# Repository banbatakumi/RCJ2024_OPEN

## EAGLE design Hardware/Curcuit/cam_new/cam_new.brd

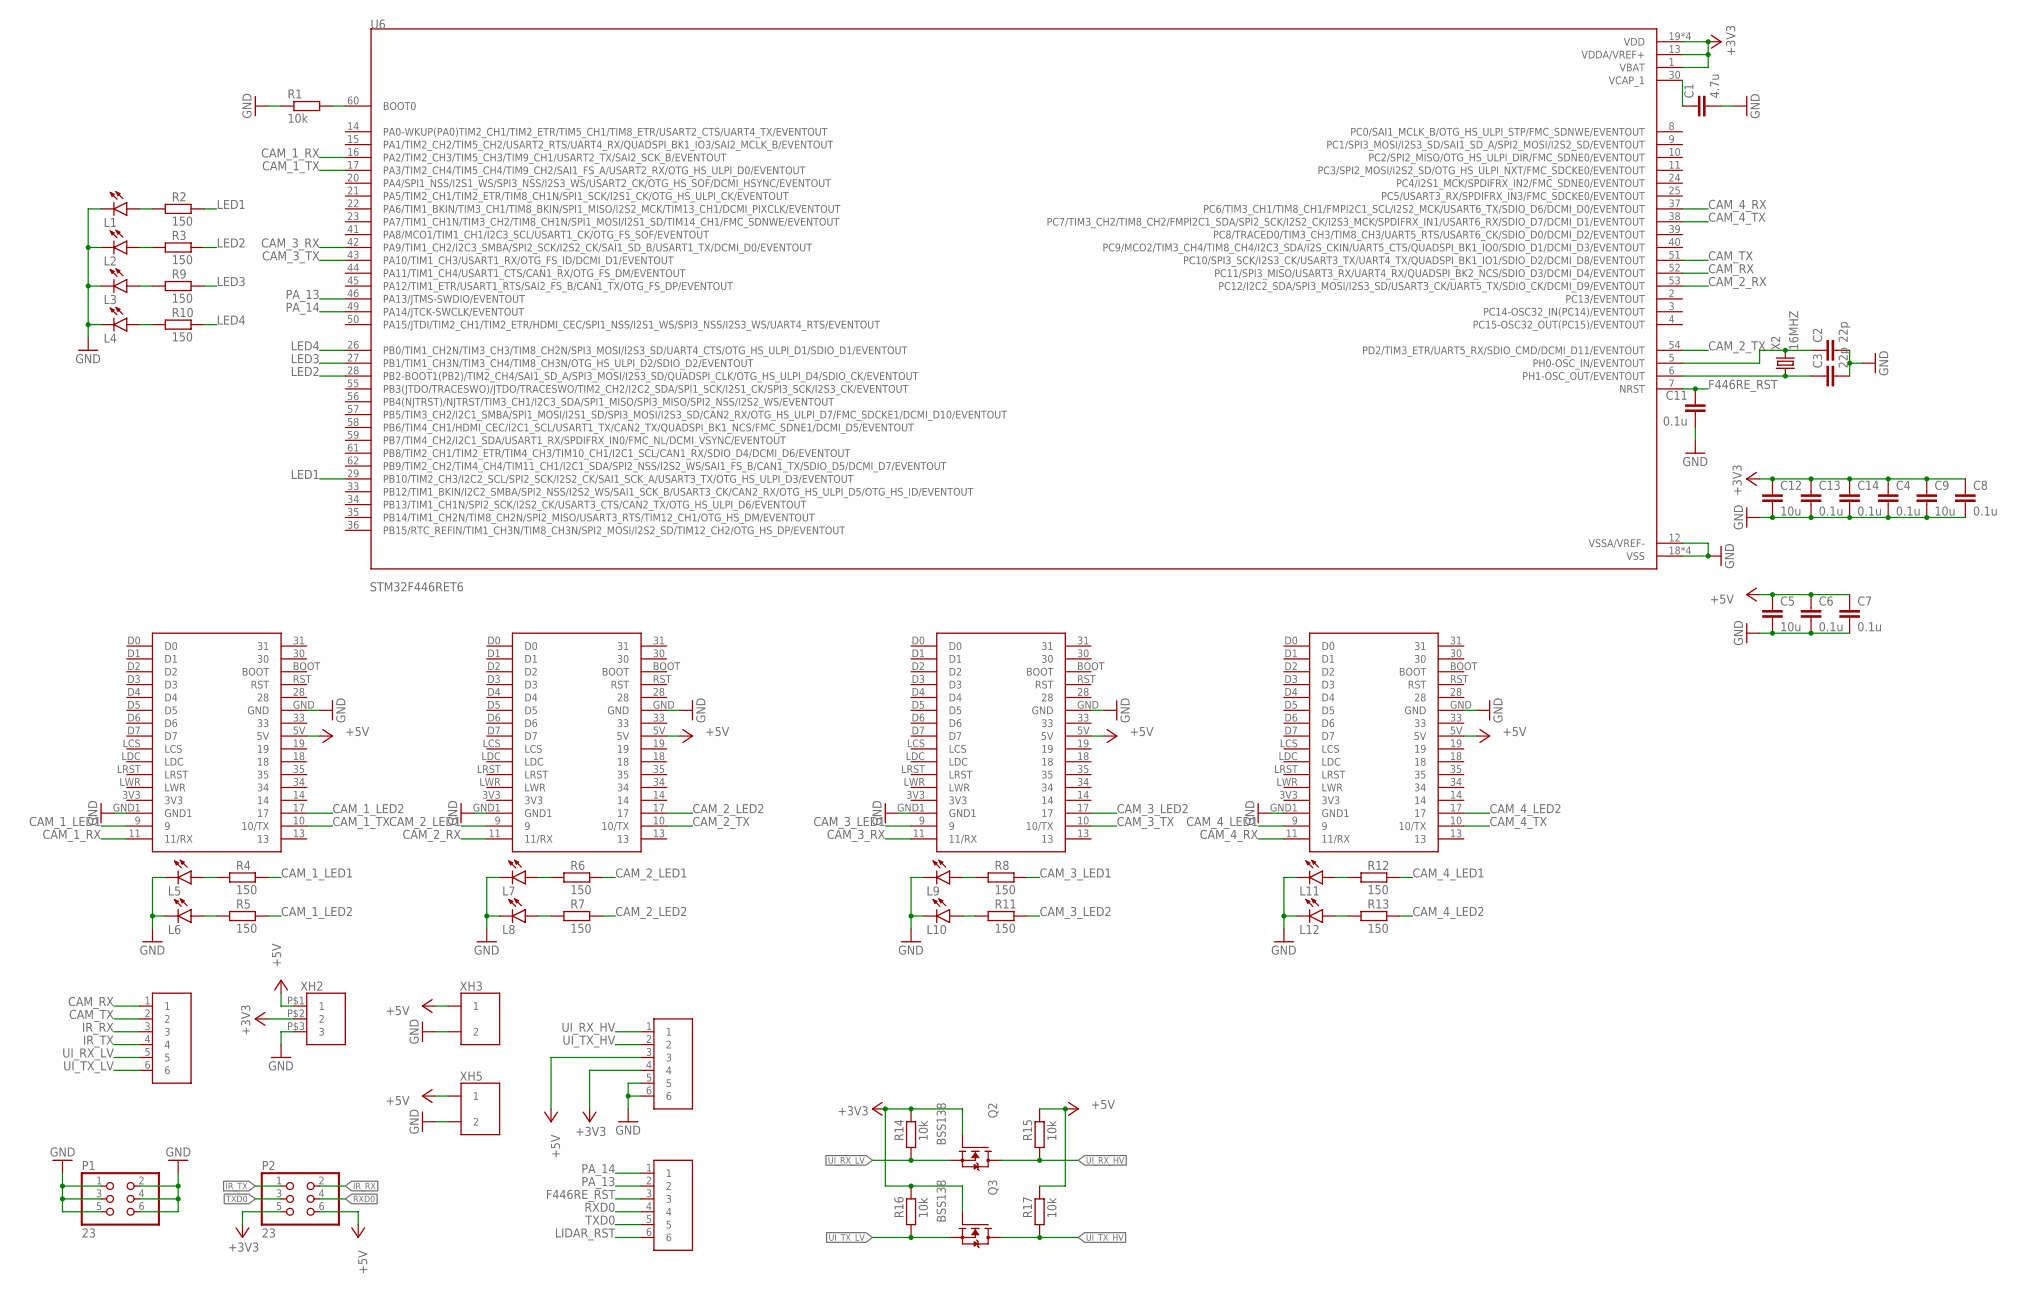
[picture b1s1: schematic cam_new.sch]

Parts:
C1: 4.7u; C0603
C2, C3: 22p; C0603
C4, C6, C7, C8, C11, C13, C14: 0.1u; C0603
C5, C9, C12: 10u; C0805
L1, L2, L3, L4, L5, L6, L7, L8, L9, L10, L11, L12: SML-E12P8WT86; LED_SML-LXFM0603SIC-TR
P1, P2: 23; 2*3
Q2, Q3: BSS138; SOT95P240X111-3N
R1, R14, R15, R16, R17: 10k; R0603
R2, R3, R4, R5, R6, R7, R8, R9, R10, R11, R12, R13: 150; R0603
U1, U2, U3, U4: M1N
U6: STM32F446RET6; QFP50P1200X1200X160-64N
X2: 16MHZ
XH1, XH4, XH6: 6B
XH2: 3B
XH3, XH5: 2B

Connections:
+3V3: C4.1, C8.1, C9.1, C12.1, C13.1, C14.1, P2.5, Q2.1 (G), Q3.1 (G), R14.2, R16.2, U6.1 (VBAT), U6.13 (VDDA/VREF+), U6.19 (VDD), U6.32 (VDD), U6.48 (VDD), U6.64 (VDD), XH2.P$2 (2), XH4.4
+5V: C5.1, C6.1, C7.1, P2.6, R15.2, R17.2, U1.5V, U2.5V, U3.5V, U4.5V, XH2.P$1 (1), XH3.P$1 (1), XH4.3, XH5.P$1 (1)
CAM_1_LED1: R4.2, U1.9
CAM_1_LED2: R5.2, U1.17
CAM_1_RX: U1.11 (11/RX), U6.16 (PA2/TIM2_CH3/TIM5_CH3/TIM9_CH1/USART2_T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)
CAM_1_TX: U1.10 (10/TX), U6.17 (PA3/TIM2_CH4/TIM5_CH4/TIM9_CH2/SAI1_FS_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)
CAM_2_LED1: R6.2, U2.9
CAM_2_LED2: R7.2, U2.17
CAM_2_RX: U2.11 (11/RX), U6.53 (PC12/I2C2_SDA/SPI3_MOSI/I2S3_SD/USART3_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)
CAM_2_TX: U2.10 (10/TX), U6.54 (PD2/TIM3_ETR/UART5_RX/SDIO_CMD/DCMI_D11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)
CAM_3_LED1: R8.2, U3.9
CAM_3_LED2: R11.2, U3.17
CAM_3_RX: U3.11 (11/RX), U6.42 (PA9/TIM1_CH2/I2C3_SMBA/SPI2_SCK/I2S2_CK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)
CAM_3_TX: U3.10 (10/TX), U6.43 (PA10/TIM1_CH3/USART1_RX/OTG_FS_ID/DCMI_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)
CAM_4_LED1: R12.2, U4.9
CAM_4_LED2: R13.2, U4.17
CAM_4_RX: U4.11 (11/RX), U6.37 (PC6/TIM3_CH1/TIM8_CH1/FMPI2C1_SCL/I2S2_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)
CAM_4_TX: U4.10 (10/TX), U6.38 (PC7/TIM3_CH2/TIM8_CH2/FMPI2C1_SDA/SPI2_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)
CAM_RX: U6.52 (PC11/SPI3_MISO/USART3_RX/UART4_RX/QUADS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), XH1.1
CAM_TX: U6.51 (PC10/SPI3_SCK/I2S3_CK/USART3_TX/UART4_T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), XH1.2
F446RE_RST: C11.1, U6.7 (NRST), XH6.3
GND: C1.2, C2.2, C3.2, C4.2, C5.2, C6.2, C7.2, C8.2, C9.2, C11.2, C12.2, C13.2, C14.2, L1.C, L2.C, L3.C, L4.C, L5.C, L6.C, L7.C, L8.C, L9.C, L10.C, L11.C, L12.C, P1.1, P1.2, P1.3, P1.4, P1.5, P1.6, R1.1, U1.GND, U1.GND1, U2.GND, U2.GND1, U3.GND, U3.GND1, U4.GND, U4.GND1, U6.12 (VSSA/VREF-), U6.18 (VSS), U6.31 (VSS), U6.47 (VSS), U6.63 (VSS), XH2.P$3 (3), XH3.P$2 (2), XH4.5, XH4.6, XH5.P$2 (2)
IR_RX: P2.2, XH1.3
IR_TX: P2.1, XH1.4
LED1: R2.2, U6.29 (PB10/TIM2_CH3/I2C2_SCL/SPI2_SCK/I2S2_CK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)
LED2: R3.2, U6.28 (PB2-BOOT1(PB2)/TIM2_CH4/SAI1_SD_A/SPI3_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)
LED3: R9.2, U6.27 (PB1/TIM1_CH3N/TIM3_CH4/TIM8_CH3N/OTG_HS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)
LED4: R10.2, U6.26 (PB0/TIM1_CH2N/TIM3_CH3/TIM8_CH2N/SPI3_M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)
LIDAR_RST: XH6.6
unnamed: C1.1, U6.30 (VCAP_1)
unnamed: R1.2, U6.60 (BOOT0)
unnamed: C2.1, U6.5 (PH0-OSC_IN/EVENTOUT), X2.P$2 (2)
unnamed: C3.1, U6.6 (PH1-OSC_OUT/EVENTOUT), X2.P$1 (1)
unnamed: L2.A, R3.1
unnamed: L4.A, R10.1
unnamed: L1.A, R2.1
unnamed: L6.A, R5.1
unnamed: L3.A, R9.1
unnamed: L5.A, R4.1
unnamed: L8.A, R7.1
unnamed: L7.A, R6.1
unnamed: L10.A, R11.1
unnamed: L9.A, R8.1
unnamed: L12.A, R13.1
unnamed: L11.A, R12.1
PA_13: U6.46 (PA13/JTMS-SWDIO/EVENTOUT), XH6.2
PA_14: U6.49 (PA14/JTCK-SWCLK/EVENTOUT), XH6.1
RXD0: P2.4, XH6.4
TXD0: P2.3, XH6.5
UI_RX_HV: Q2.3 (D), R15.1, XH4.1
UI_RX_LV: Q2.2 (S), R14.1, XH1.5
UI_TX_HV: Q3.3 (D), R17.1, XH4.2
UI_TX_LV: Q3.2 (S), R16.1, XH1.6

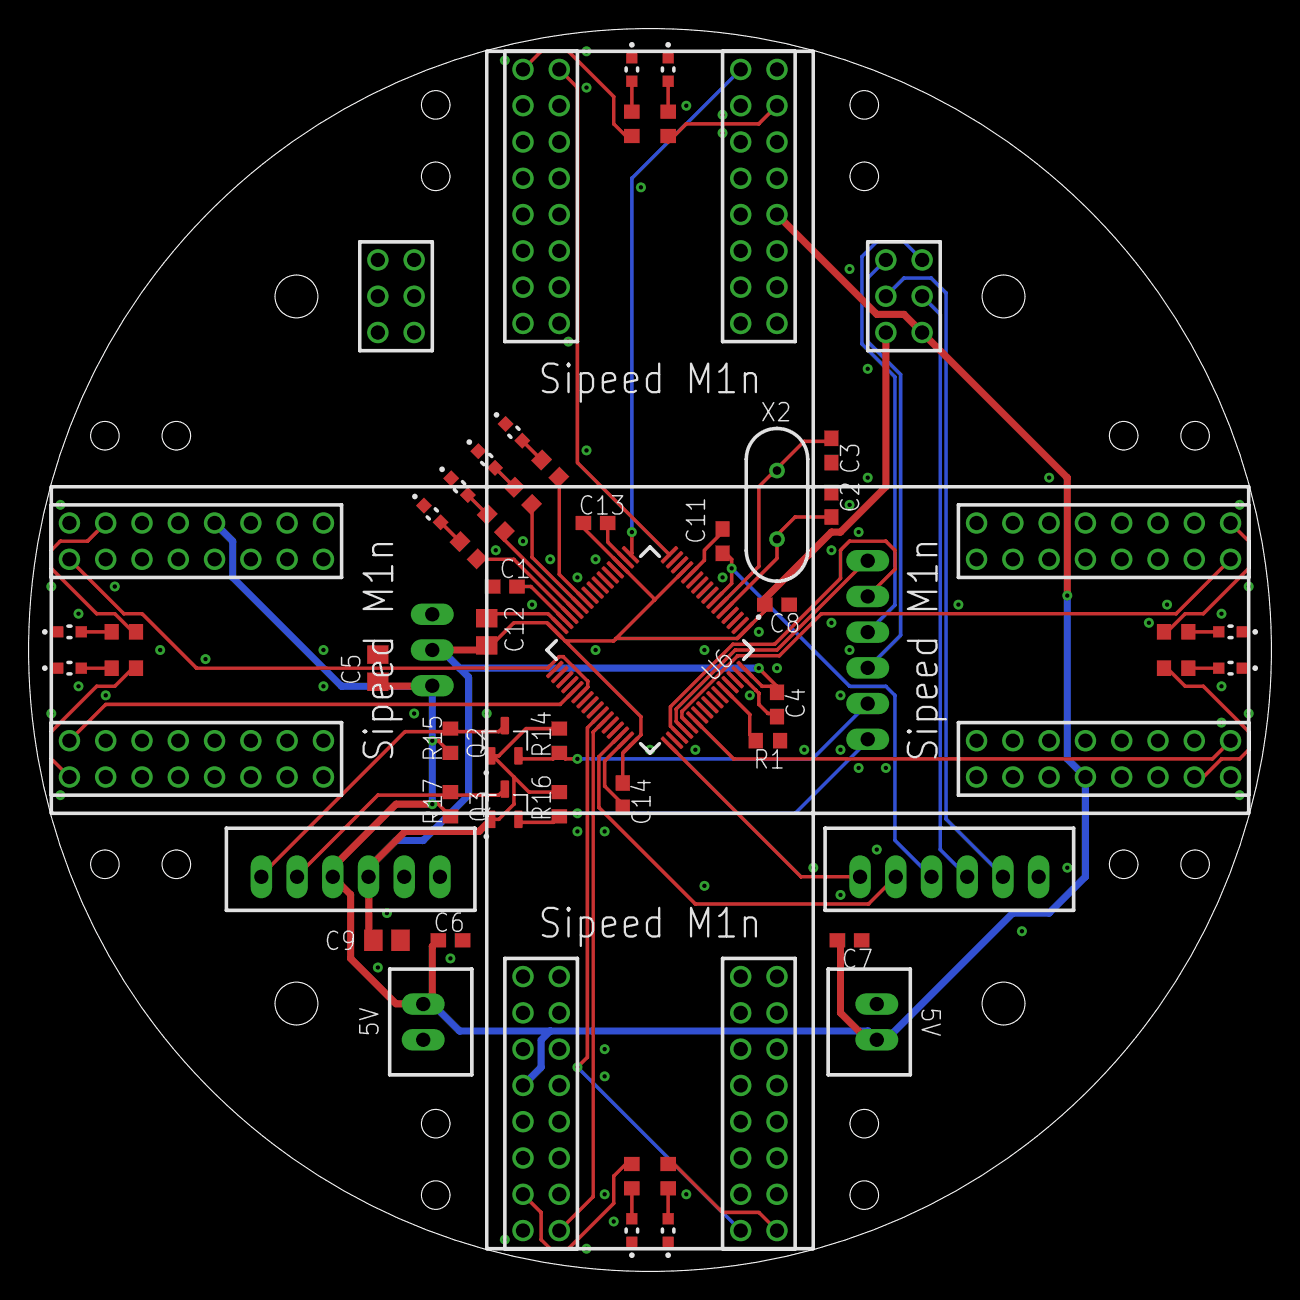
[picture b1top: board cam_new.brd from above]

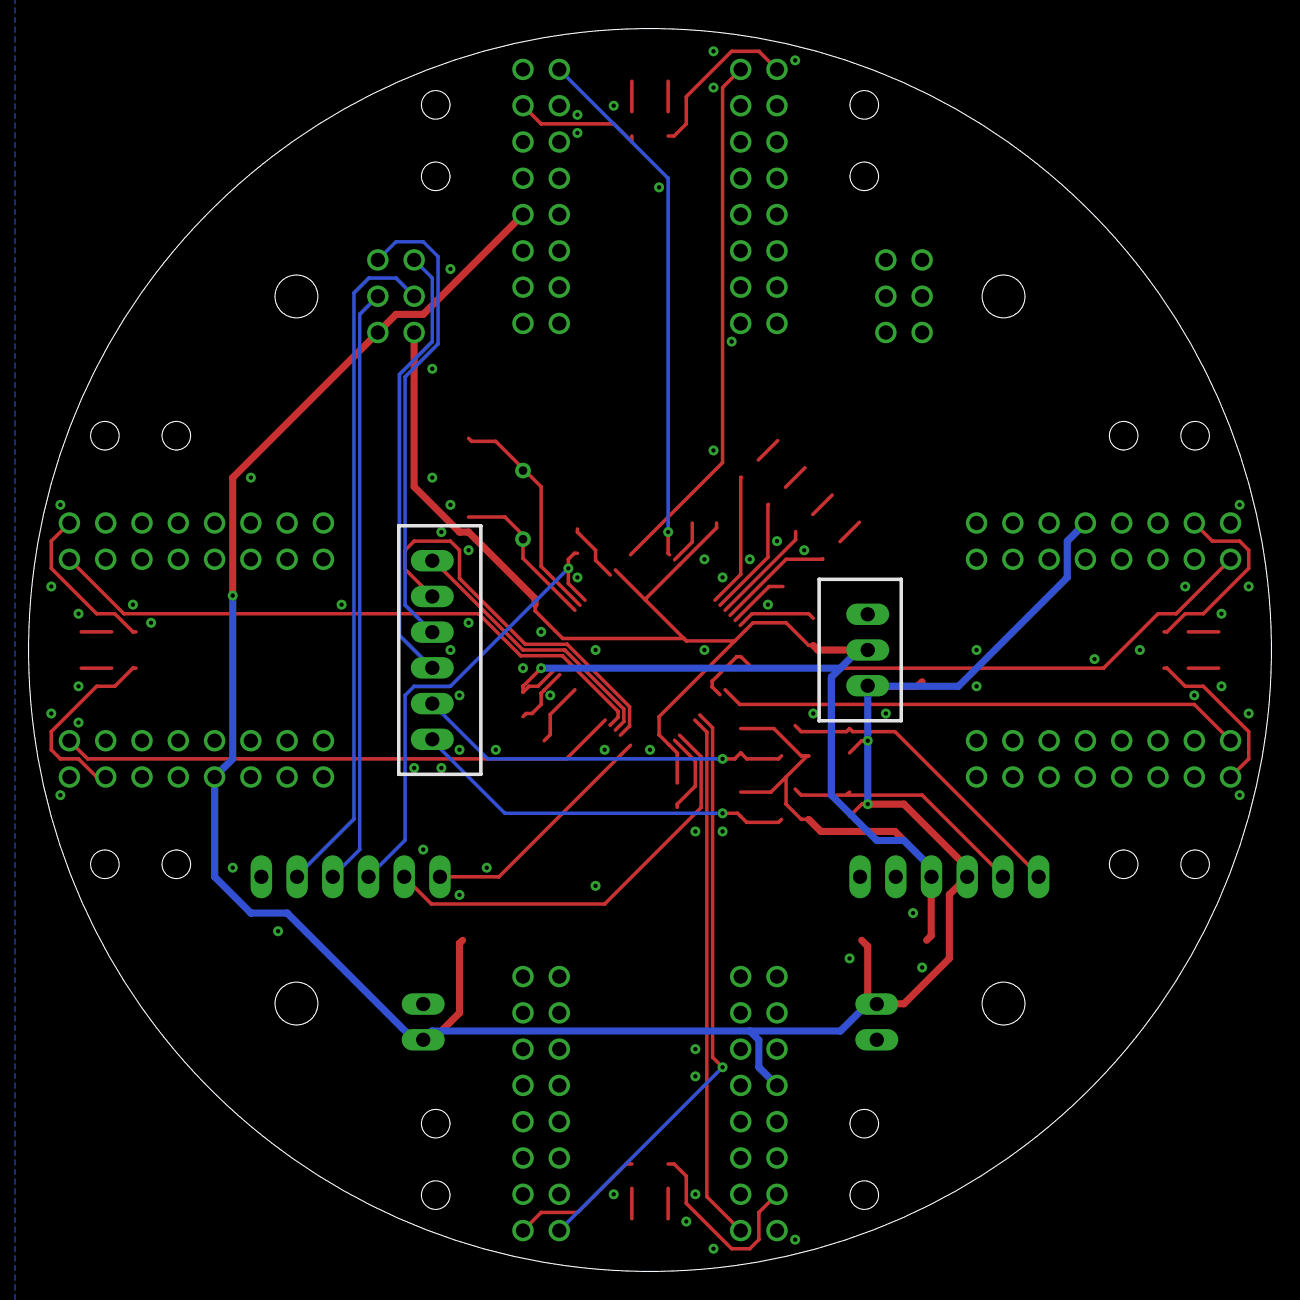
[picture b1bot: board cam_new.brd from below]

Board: 2 copper layers, 87.0 x 87.0 mm, 58 parts (2 on the bottom side), 52 nets.

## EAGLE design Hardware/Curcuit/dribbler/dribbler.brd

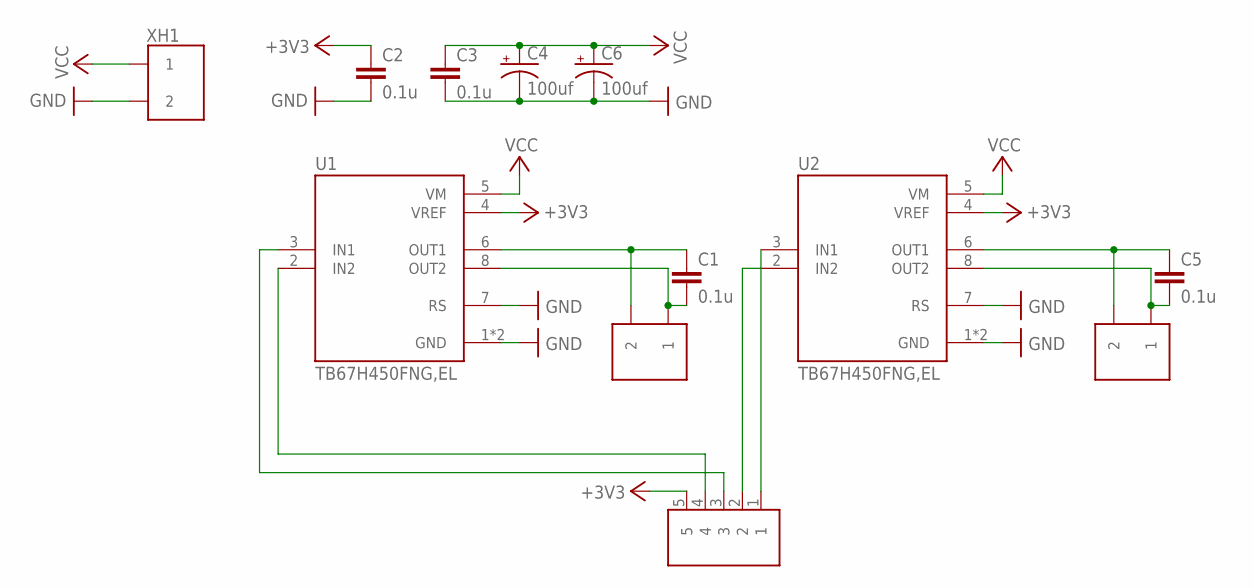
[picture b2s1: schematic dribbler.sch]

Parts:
C1, C2, C3, C5: 0.1u; C0603
C4, C6: 100uf; MH5
U1, U2: TB67H450FNG,EL; SOIC127P599X175-9N
U$1, U$3: S2B
U$2: S5B
XH1: S2B

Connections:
+3V3: C2.1, U1.4 (VREF), U2.4 (VREF), U$2.5
GND: C2.2, C3.2, C4.-, C6.-, U1.1 (GND), U1.7 (RS), U1.9 (GND), U2.1 (GND), U2.7 (RS), U2.9 (GND), XH1.2
unnamed: C5.1, U2.6 (OUT1), U$3.2
unnamed: C1.2, U1.8 (OUT2), U$1.1
unnamed: U1.3 (IN1), U$2.3
unnamed: U1.2 (IN2), U$2.4
unnamed: C5.2, U2.8 (OUT2), U$3.1
unnamed: U2.2 (IN2), U$2.2
unnamed: U2.3 (IN1), U$2.1
unnamed: C1.1, U1.6 (OUT1), U$1.2
VCC: C3.1, C4.+, C6.+, U1.5 (VM), U2.5 (VM), XH1.1

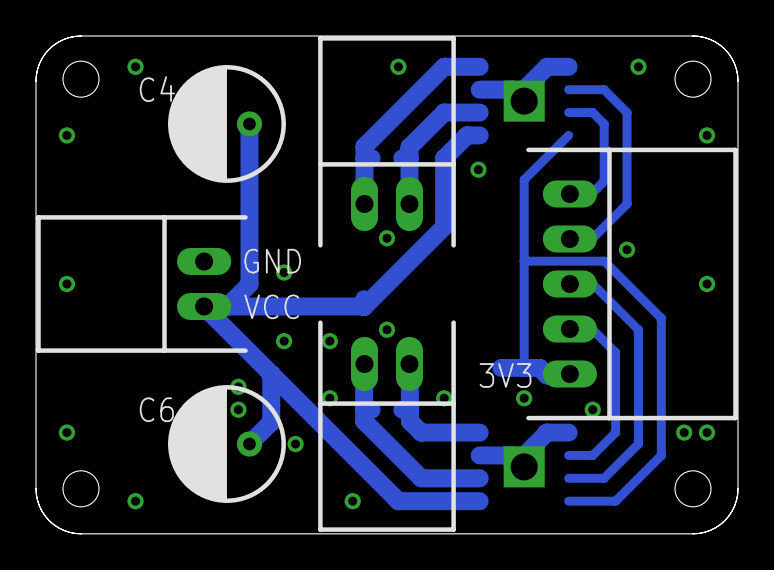
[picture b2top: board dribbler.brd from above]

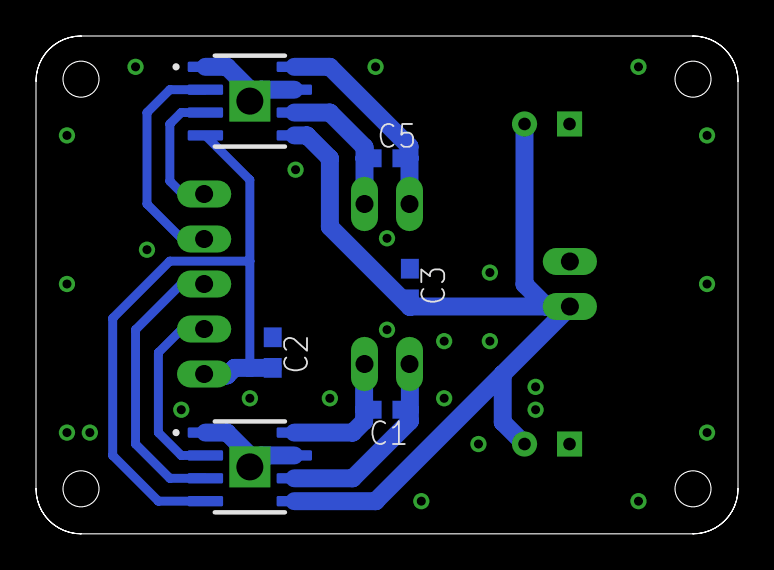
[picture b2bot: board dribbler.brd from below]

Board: 2 copper layers, 39.0 x 27.7 mm, 12 parts (6 on the bottom side), 11 nets.

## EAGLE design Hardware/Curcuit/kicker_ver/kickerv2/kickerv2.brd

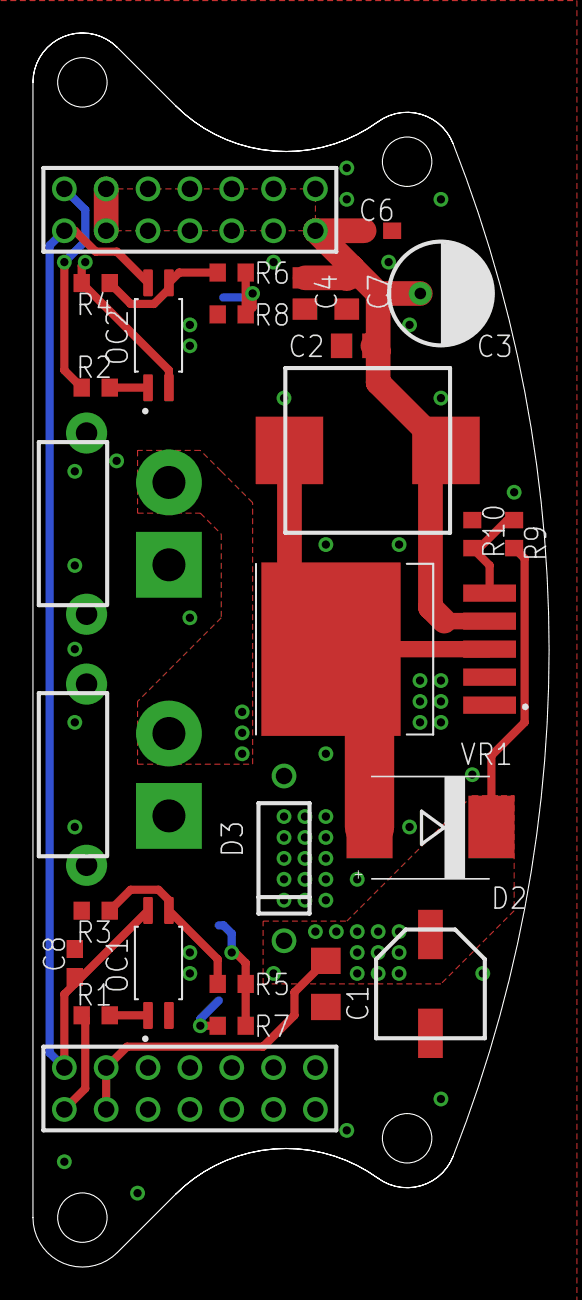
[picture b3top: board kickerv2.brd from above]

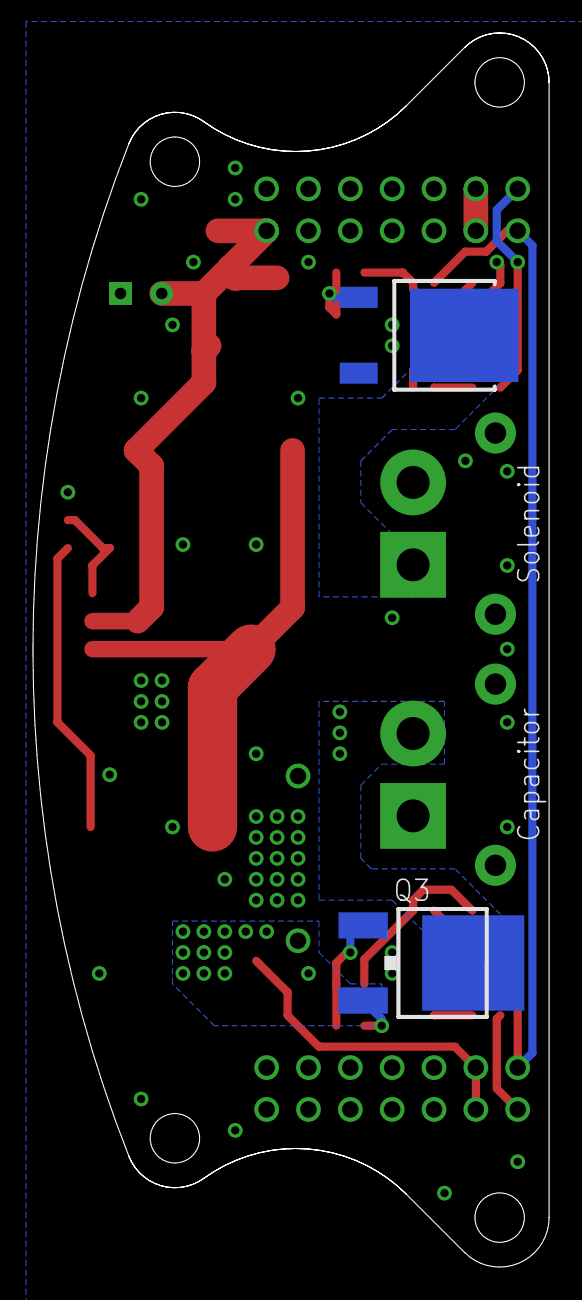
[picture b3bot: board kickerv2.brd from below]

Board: 2 copper layers, 31.3 x 74.9 mm, 30 parts (2 on the bottom side), 16 nets.

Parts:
C1: 1uf; C1206
C2, C4, C7: 22uf; C0805
C3: 100uf; MH5
C5: 47uf; VZ1H470ME077000CE0
C6, C8: 0.1uf; C0603
D2: SS1060C; DIOSC6959X240
D3: UF2010
L1: 47uh; MDE1040-470M
OC1, OC2: TL293(GB); SOIC127P700X230-4N
Q2: NP52N06SLG; TO230P1040X230-3N
Q3: TJ60S04M3L; DPACK
R1, R2, R5, R6: 100; R0603
R3, R4: 1k; R0603
R7, R8: 10k; R0603
R9: 62k; R0603
R10: 2k; R0603
U$2, U$3: 27; 2*7
VR1: XL6009; DPAK170P1435X465-6N
XT1, XT2: XT30PW-F

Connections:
40V: C1.1, C5.+, D2.C, D3.C, Q3.S, R7.1, R9.2, U$2.11, U$2.12
+5V: C8.1, OC1.COL, OC2.COL, U$2.13, U$3.14
GND: C1.2, C2.2, C3.-, C4.2, C5.-, C6.2, C7.2, C8.2, D3.A, OC1.C, OC2.C, Q2.S, R3.1, R4.2, R8.1, R10.1, U$2.1, U$2.2, U$2.3, U$2.4, U$2.5, U$2.6, U$2.7, U$2.8, U$2.9, U$2.10, VR1.1, XT1.-
unnamed: Q3.D, XT1.+, XT2.+
unnamed: Q2.D, XT2.-
unnamed: OC1.EMI, R3.2, R5.2
unnamed: R9.1, R10.2, VR1.5
unnamed: OC1.A, R1.1
unnamed: OC2.A, R2.2
unnamed: OC2.EMI, R4.1, R6.2
unnamed: D2.A, L1.P$2, VR1.3, VR1.6
unnamed: Q3.G, R5.1, R7.2
unnamed: Q2.G, R6.1, R8.2
SIG1: R1.2, U$2.14
SIG2: R2.1, U$3.13
VCC: C2.1, C3.+, C4.1, C6.1, C7.1, L1.P$1, U$3.1, U$3.2, U$3.3, U$3.4, U$3.5, U$3.6, U$3.7, U$3.8, U$3.9, U$3.10, U$3.11, U$3.12, VR1.4

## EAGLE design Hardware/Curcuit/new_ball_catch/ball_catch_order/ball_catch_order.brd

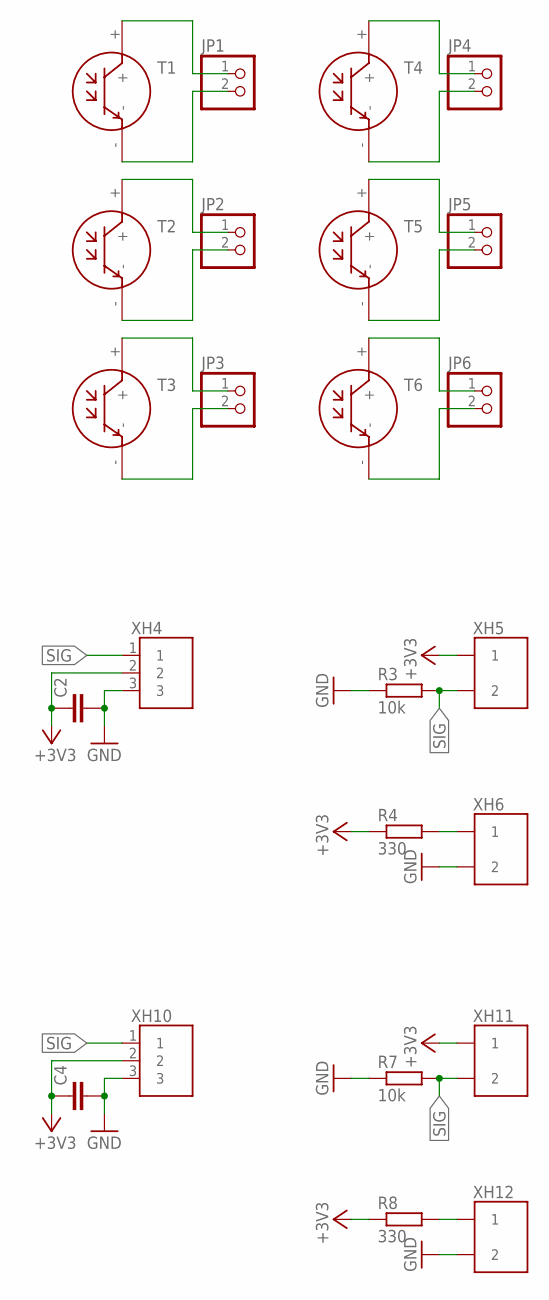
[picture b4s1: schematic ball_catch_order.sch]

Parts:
C2, C4: C-EUC0603; C0603
JP1, JP2, JP3, JP4, JP5, JP6: PINHD-1X2; 1X02
R3, R7: 10k; 0204/7
R4, R8: 330; 0204/7
T1, T2, T3, T4, T5, T6: NJL7302L-F3
XH4, XH10: S3B
XH5, XH11: 2B
XH6, XH12: S2B

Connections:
+3V3: C2.1, C4.1, R4.1, R8.1, XH4.2, XH5.1, XH10.2, XH11.1
GND: C2.2, C4.2, R3.1, R7.1, XH4.3, XH6.2, XH10.3, XH12.2
unnamed: JP1.1, T1.+
unnamed: JP1.2, T1.-
unnamed: JP2.1, T2.+
unnamed: JP2.2, T2.-
unnamed: JP3.1, T3.+
unnamed: JP3.2, T3.-
unnamed: JP4.1, T4.+
unnamed: JP4.2, T4.-
unnamed: JP5.1, T5.+
unnamed: JP5.2, T5.-
unnamed: JP6.1, T6.+
unnamed: JP6.2, T6.-
unnamed: R4.2, XH6.1
unnamed: R8.2, XH12.1
SIG: R3.2, R7.2, XH4.1, XH5.2, XH10.1, XH11.2

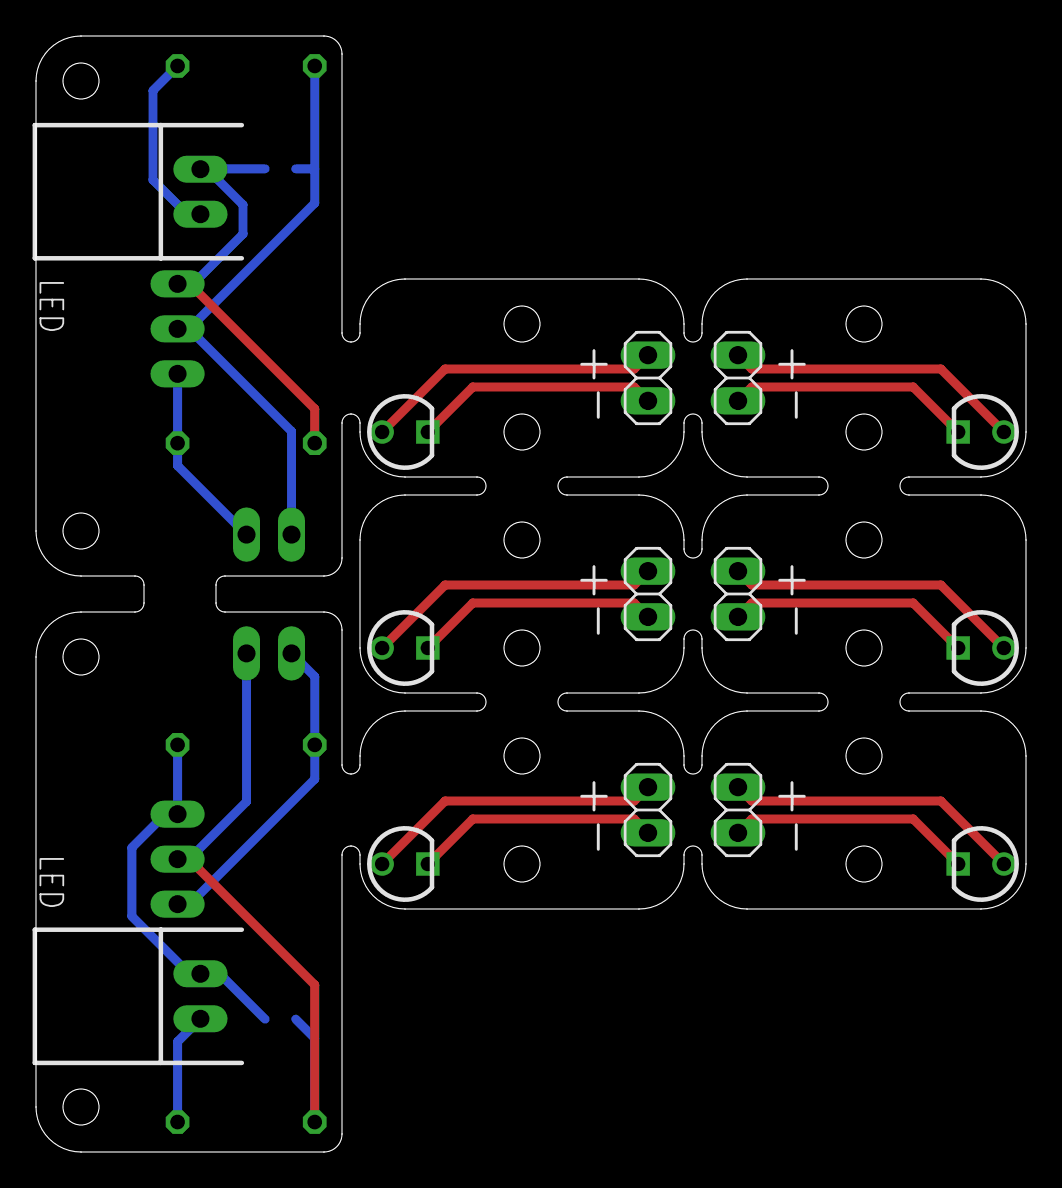
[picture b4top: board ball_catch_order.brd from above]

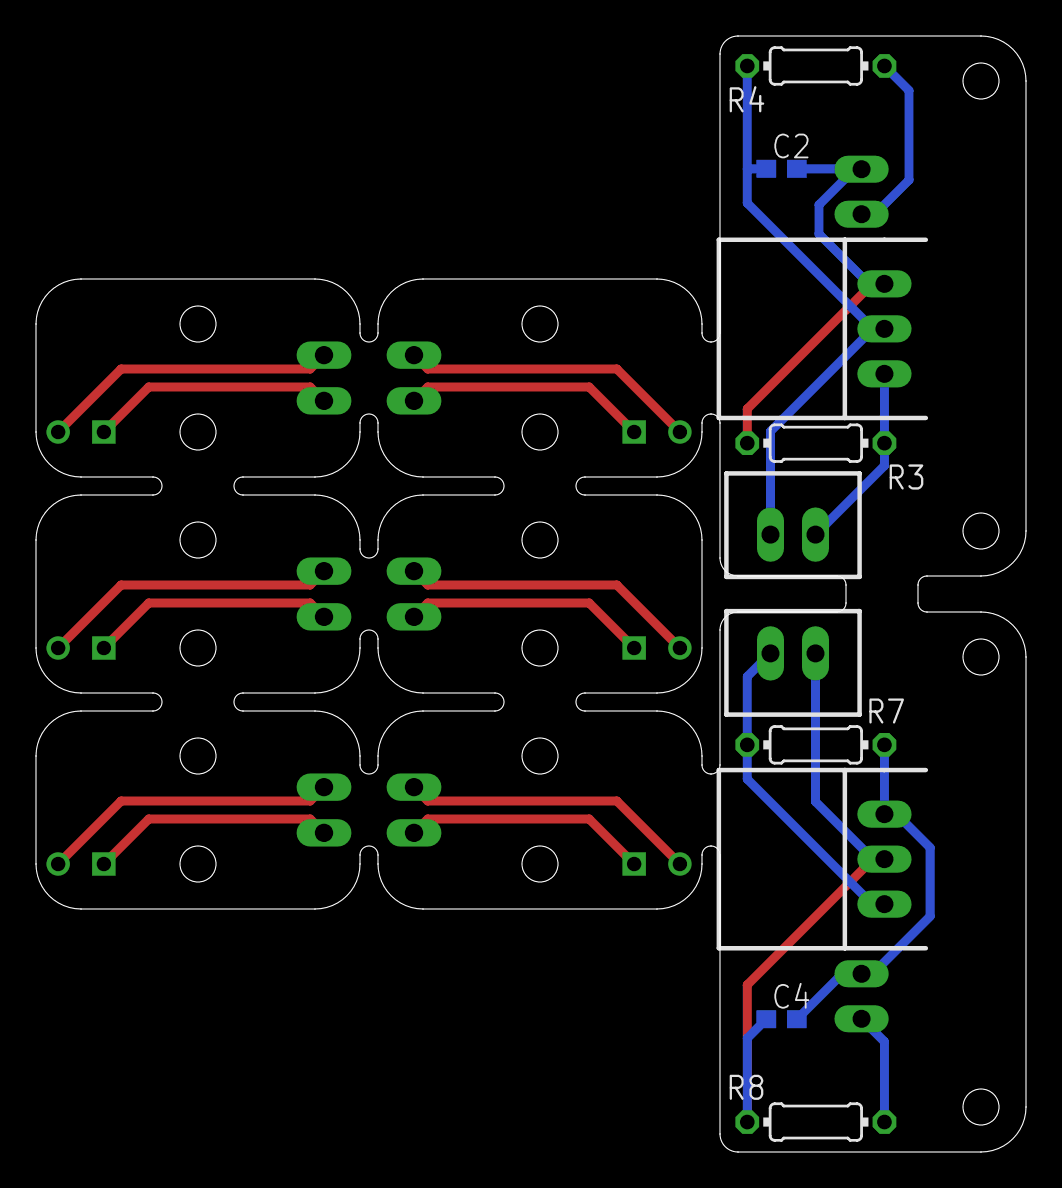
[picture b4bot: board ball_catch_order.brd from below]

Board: 2 copper layers, 55.0 x 62.0 mm, 24 parts (10 on the bottom side), 17 nets.

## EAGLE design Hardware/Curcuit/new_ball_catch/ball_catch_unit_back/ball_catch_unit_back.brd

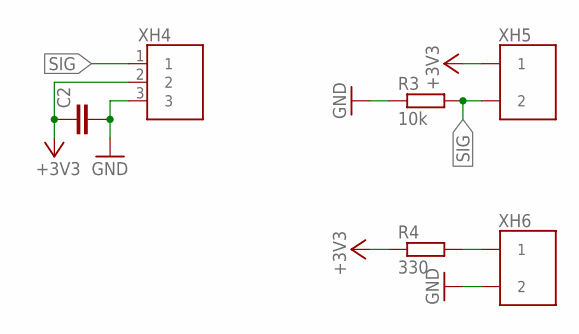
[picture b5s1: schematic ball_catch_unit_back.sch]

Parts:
C2: C-EUC0603; C0603
R3: 10k; 0204/7
R4: 330; 0204/7
XH4: S3B
XH5: 2B
XH6: S2B

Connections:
+3V3: C2.1, R4.1, XH4.2, XH5.1
GND: C2.2, R3.1, XH4.3, XH6.2
unnamed: R4.2, XH6.1
SIG: R3.2, XH4.1, XH5.2

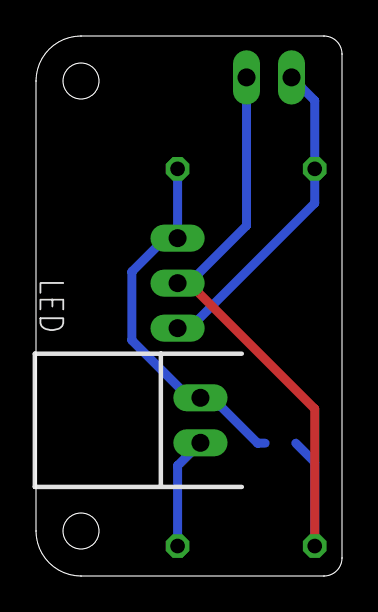
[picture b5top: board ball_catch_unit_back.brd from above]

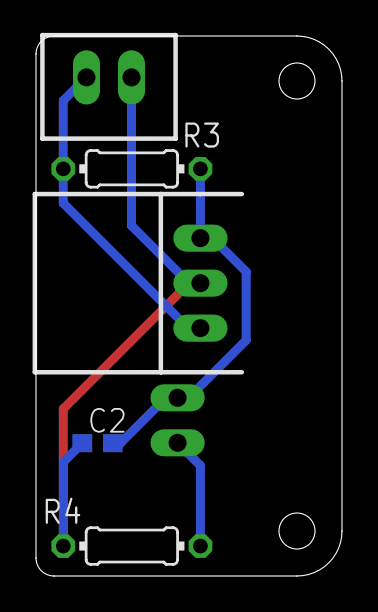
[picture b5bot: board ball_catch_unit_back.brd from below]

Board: 2 copper layers, 17.0 x 30.0 mm, 6 parts (5 on the bottom side), 4 nets.

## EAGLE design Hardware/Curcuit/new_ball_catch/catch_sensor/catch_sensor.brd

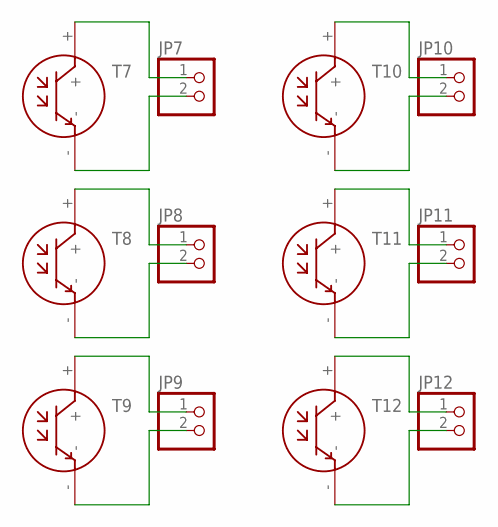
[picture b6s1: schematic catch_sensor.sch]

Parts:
JP7, JP8, JP9, JP10, JP11, JP12: PINHD-1X2; 1X02
T7, T8, T9, T10, T11, T12: NJL7302L-F3

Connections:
unnamed: JP7.1, T7.+
unnamed: JP7.2, T7.-
unnamed: JP8.1, T8.+
unnamed: JP8.2, T8.-
unnamed: JP9.1, T9.+
unnamed: JP9.2, T9.-
unnamed: JP10.1, T10.+
unnamed: JP10.2, T10.-
unnamed: JP11.1, T11.+
unnamed: JP11.2, T11.-
unnamed: JP12.1, T12.+
unnamed: JP12.2, T12.-

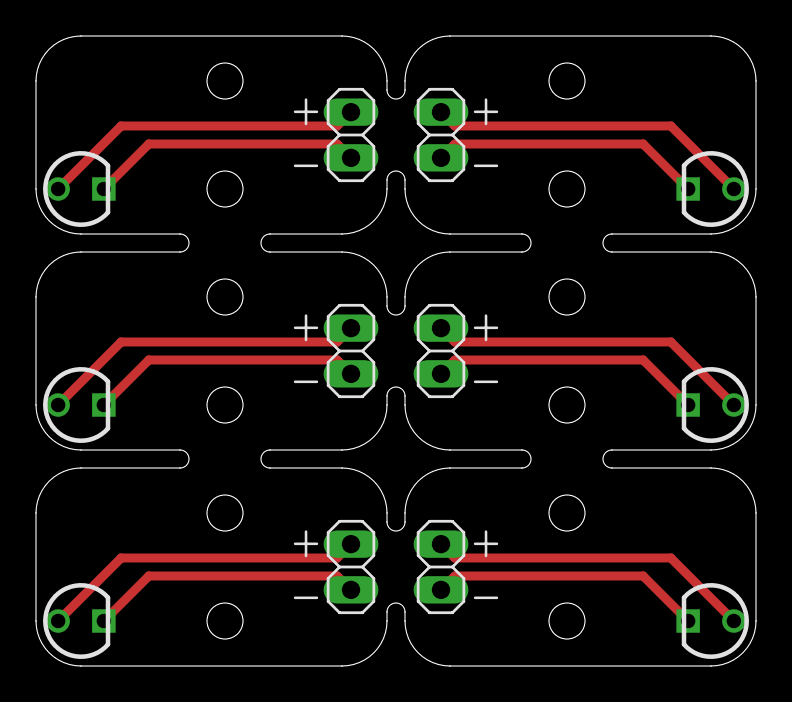
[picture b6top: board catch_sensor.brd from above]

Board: 2 copper layers, 40.0 x 35.0 mm, 12 parts (0 on the bottom side), 12 nets.

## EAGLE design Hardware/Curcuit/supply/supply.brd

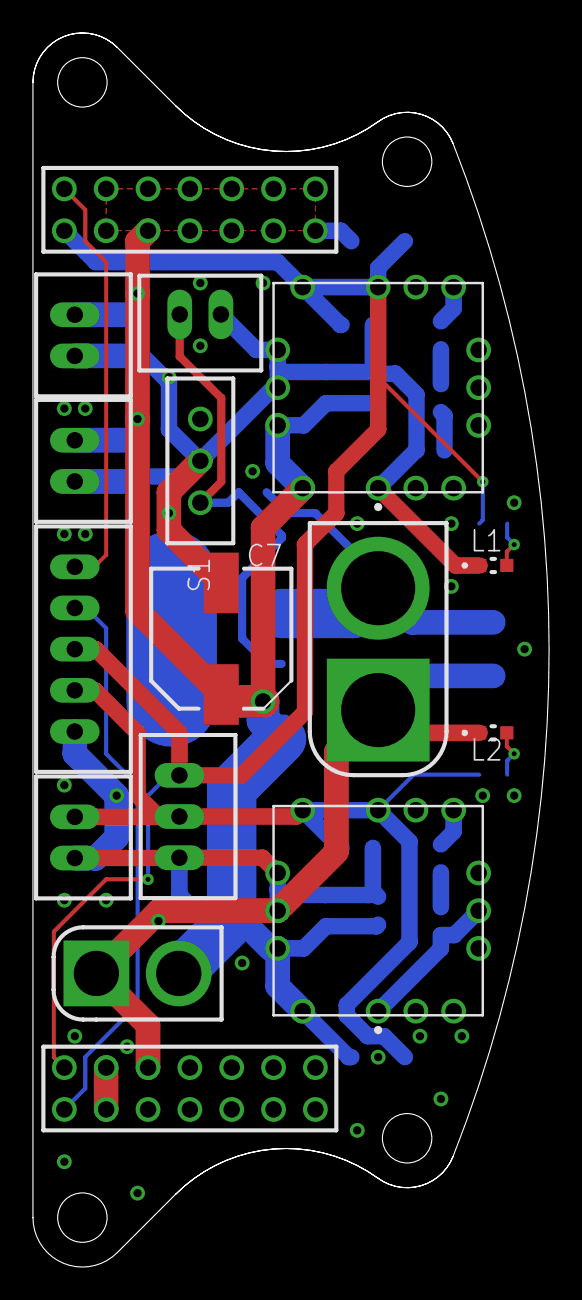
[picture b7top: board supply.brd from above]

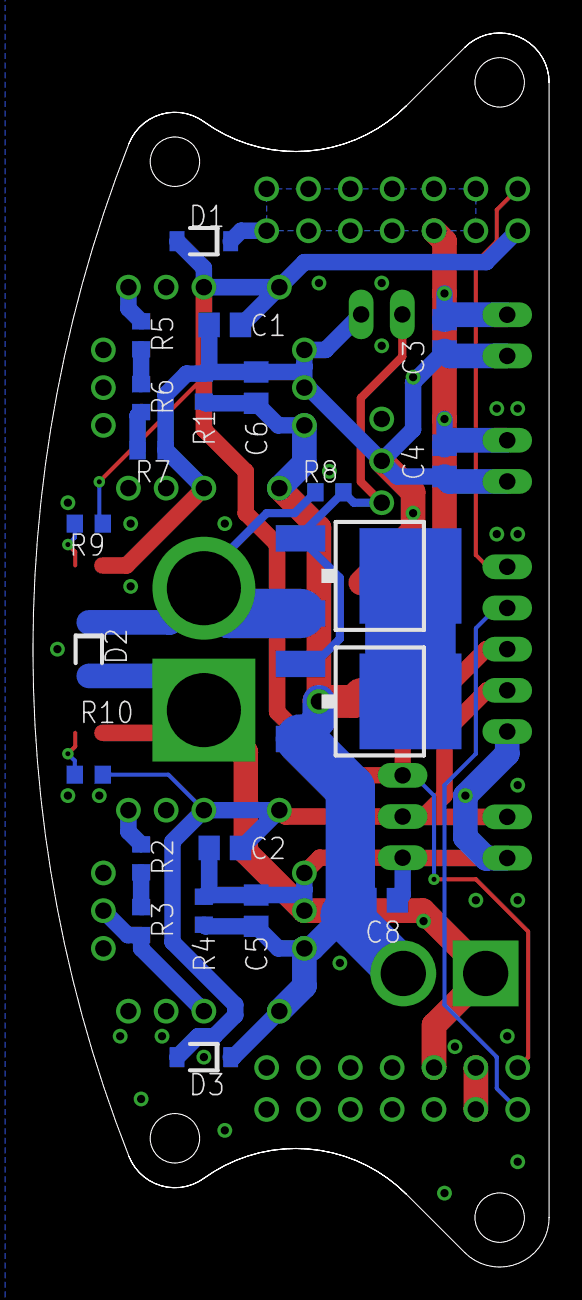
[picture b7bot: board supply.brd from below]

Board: 2 copper layers, 31.3 x 74.9 mm, 38 parts (22 on the bottom side), 17 nets.

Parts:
C1, C2, C3, C4, C8: 10u; C0805
C5, C6: 22u; C0805
C7: 220u; CAPAE830X1080N
D1, D2, D3: SS2040FL; SOD123FL
L1, L2: SML-E12P8WT86; LED_SML-LXFM0603SIC-TR
MD1, MD2: OKL-T/6-W12N-CMURATA_OKL-T-6-W12N-C_0_0; MURATA_OKL-T-6-W12N-C_0
R1, R4: 20k; R0603
R2: 1.5k; R0603
R3: 680; R0603
R5: 1k; R0603
R6, R9: 330; R0603
R7: 10; R0603
R8: 10k; R0603
R10: 150; R0603
S1: SS-12SDP2
U1, U2: TJ60S04M3L; DPACK
U$1, U$2: 27; 2*7
XH1, XH3, XH4, XH6: 2B
XH2: 5B
XH5: 3B
XT1: XT60U-M
XT3: XT30U-M

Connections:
40V: U$1.3, U$1.4
+3V3: C2.1, D3.A, MD1.4, MD1.5, R10.2, XH2.4, XH5.P$2, XH6.P$1
+5V: C1.1, D1.A, MD2.4, MD2.5, R9.2, U$1.2, U$2.1, XH2.3, XH5.P$1
GND: C1.2, C2.2, C3.1, C4.1, C5.1, C6.1, C7.-, C8.1, D2.A, L1.C, L2.C, MD1.1, MD1.3_1, MD1.3_2, MD1.7, MD2.1, MD2.3_1, MD2.3_2, MD2.7, R1.2, R3.2, R4.2, R7.1, S1.2, U$1.5, U$1.6, U$1.7, U$1.8, U$1.9, U$1.10, U$1.11, U$1.12, U$1.13, U$1.14, XH1.P$1, XH2.5, XH3.P$2, XH4.P$2, XH5.P$3, XH6.P$2, XT1.-, XT3.-
unnamed: MD1.6, R2.1
unnamed: R2.2, R3.1
unnamed: MD2.6, R5.1
unnamed: R5.2, R6.1
unnamed: R6.2, R7.2
unnamed: R8.1, S1.1, U1.G, U2.G, XH1.P$2
unnamed: D2.C, R8.2, U1.S, XT1.+
unnamed: U1.D, U2.D
unnamed: U$1.1, XH2.2
unnamed: U$2.2, XH2.1
unnamed: L1.A, R9.1
unnamed: L2.A, R10.1
VCC: C3.2, C4.2, C5.2, C6.2, C7.+, C8.2, D1.C, D3.C, MD1.2_1, MD1.2_2, MD2.2_1, MD2.2_2, R1.1, R4.1, U2.S, U$2.3, U$2.4, U$2.5, U$2.6, U$2.7, U$2.8, U$2.9, U$2.10, U$2.11, U$2.12, U$2.13, U$2.14, XH3.P$1, XH4.P$1, XT3.+
